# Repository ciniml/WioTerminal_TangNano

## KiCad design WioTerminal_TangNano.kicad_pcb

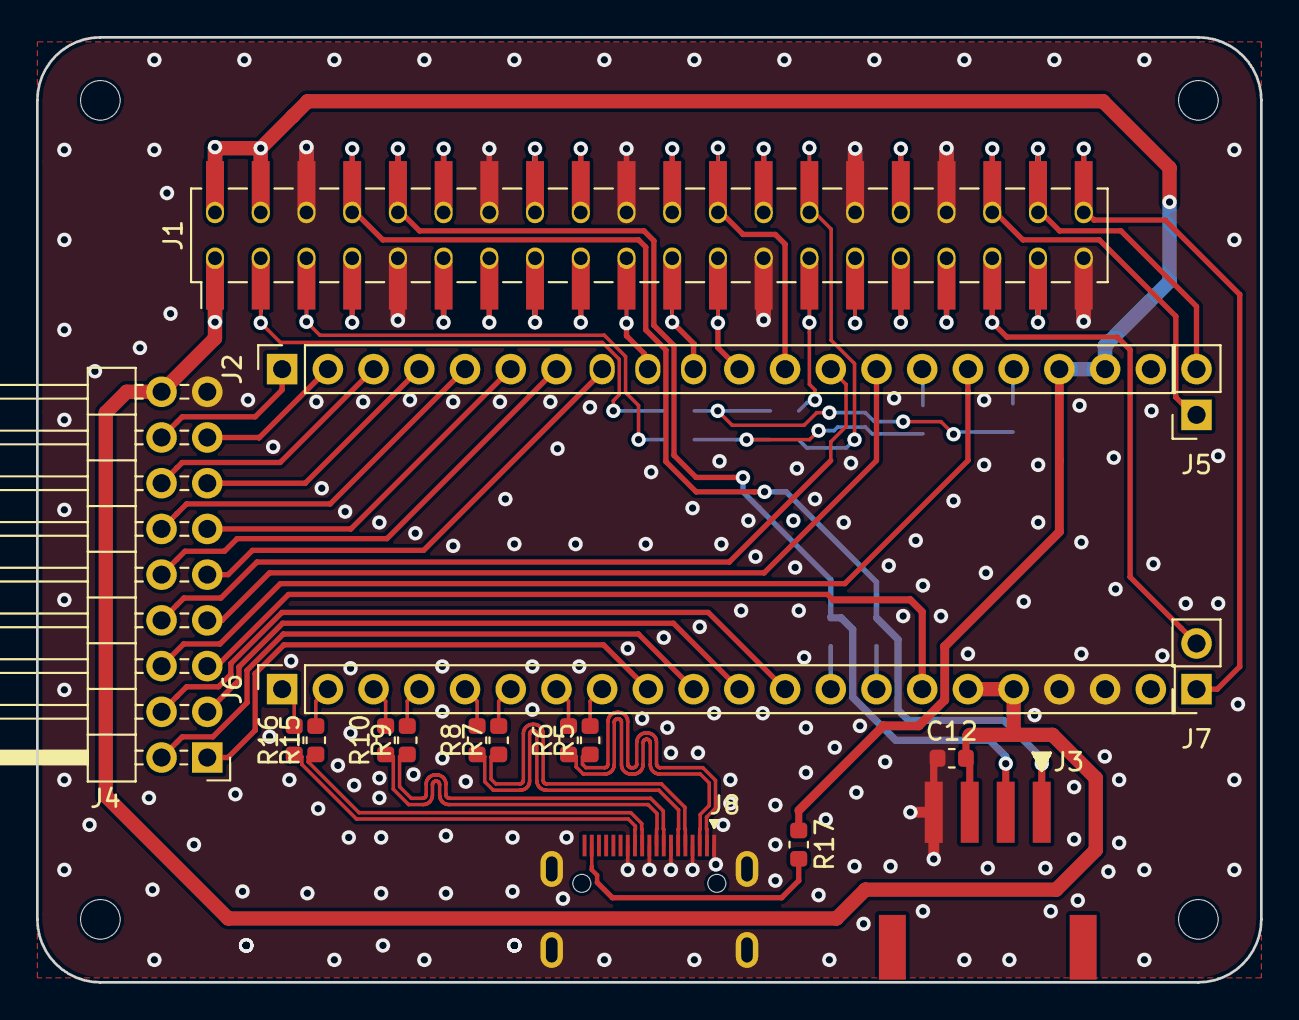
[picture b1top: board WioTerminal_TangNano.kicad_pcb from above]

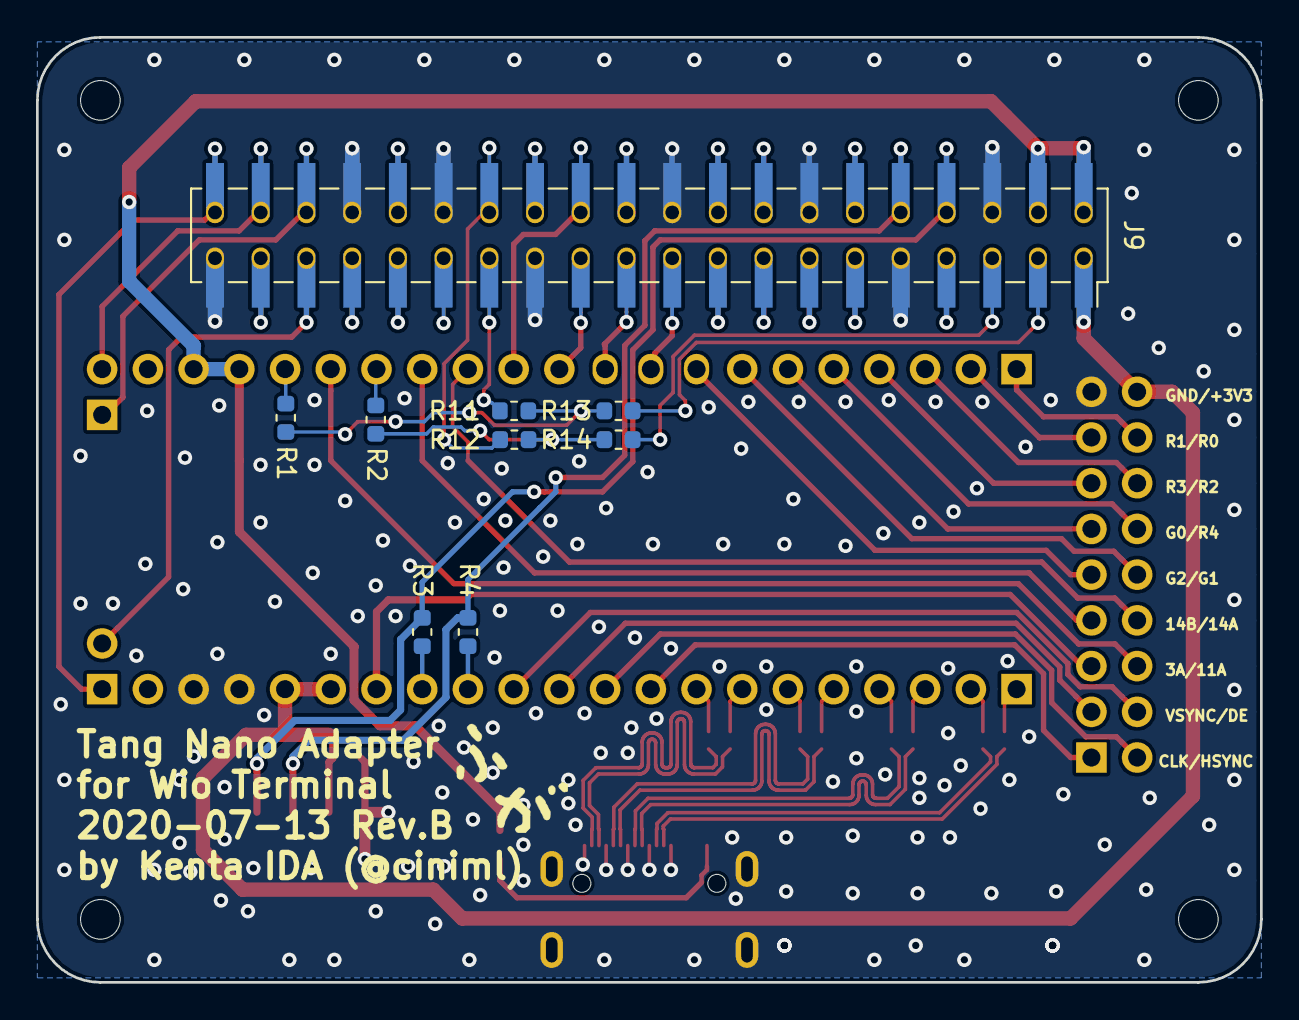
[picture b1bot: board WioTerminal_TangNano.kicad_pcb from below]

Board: 2 copper layers, 68.0 x 52.5 mm, 32 parts (10 on the bottom side), 70 nets.

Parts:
C12: 1u; C_0603_1608Metric
J1: Raspberry_Pi_2_3; PinHeader_2x20_P2.54mm_Vertical_SMD
J2: TangNano_Left; PinSocket_1x20_P2.54mm_Vertical
J3: GROVE; PHS-4AW
J4: Conn_01x18; PinHeader_2x09_P2.54mm_Horizontal
J5: TangNano_JTAG_L; PinSocket_1x02_P2.54mm_Vertical
J6: TangNano_Right; PinSocket_1x20_P2.54mm_Vertical
J7: TangNano_JTAG_R; PinSocket_1x02_P2.54mm_Vertical
J8: HDMI_C_1.3; SOFNG-HDMI-519
J9: Raspberry_Pi_2_3; PinSocket_2x20_P2.54mm_Vertical_SMD
LOGO1: Logo_Open_Hardware_Small; logo
MH1, MH2, MH3, MH4: Corner; MountingHole_2.2mm_M2_DIN965
R1, R2, R3, R4, R13, R14: DNP; R_0603_1608Metric
R5, R6, R7, R8, R9, R10, R15, R16: 240; R_0603_1608Metric
R11, R12: 0; R_0603_1608Metric
R17: 10; R_0603_1608Metric

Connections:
+3V3: C12.1, J1.1, J1.17, J3.3, J4.18, J6.16, J6.17, J9.1, J9.17
+5V: J1.2, J1.4, J2.18, J2.19, J9.2, J9.4, R17.1
/B0: J6.4, R9.2
/B1: J6.5, R8.2
/B2: J6.6, R7.2
/B3: J6.7, R6.2
/B4: J6.8, R5.2
/CE1: J1.26, J9.26
/CH552_RX0: J6.13, R4.1
/CH552_TX0: J6.14, R3.1
/G0: J2.6, J4.11
/G1: J2.7, J4.10
/G2: J2.8, J4.9
/G3: J6.1, R16.2
/G4: J6.2, R15.2
/G5: J6.3, R10.2
/GCLK0: J1.7, J9.7
/GCLK1: J1.29, J9.29
/GCLK2: J1.31, J9.31
/GPIO17: J1.11, J9.11
/GPIO18: J1.12, J9.12
/GPIO22: J1.15, J9.15
/GPIO23: J1.16, J9.16
/GPIO24: J1.18, J9.18
/GPIO25: J1.22, J9.22
/GPIO26: J1.37, J9.37
/GPIO27: J1.13, J9.13
/HDMI_CK_N: J8.12, R16.1
/HDMI_CK_P: J8.11, R15.1
/HDMI_D0_N: J8.9, R10.1
/HDMI_D0_P: J8.8, R9.1
/HDMI_D1_N: J8.6, R8.1
/HDMI_D1_P: J8.5, R7.1
/HDMI_D2_N: J8.3, R6.1
/HDMI_D2_P: J8.2, R5.1
/I2C0_SCL: J1.28, J9.28, R12.2
/I2C0_SDA: J1.27, J9.27, R11.2
/I2C1_SCL: J1.5, J9.5, R14.2
/I2C1_SDA: J1.3, J9.3, R13.2
/IOB3A: J4.5, J6.15
/IOB7A: J1.19, J2.9, J9.19
/IOB10A: J1.21, J2.10, J9.21
/IOB10B: J1.23, J2.11, J9.23
/IOB11B: J1.24, J2.12, J9.24
/IOB14A: J2.13, J4.8
/IOB14B: J2.14, J4.7
/IOB16A: J2.17, R1.1
/IOB16B: J2.15, R2.1
/IOV11A: J2.16, J4.6
/LCD_CLK: J4.1, J6.9
/LCD_DE: J4.4, J6.12
/LCD_HSYNC: J4.2, J6.10
/LCD_VSYNC: J4.3, J6.11
/PWM0: J1.32, J9.32
/PWM1: J1.33, J9.33
/R0: J2.1, J4.16
/R1: J2.2, J4.15
/R2: J2.3, J4.14
/R3: J2.4, J4.13
/R4: J2.5, J4.12
/RXD: J1.10, J3.2, J9.10, R4.2
/SCL: R2.2, R12.1, R14.1
/SDA: R1.2, R11.1, R13.1
/TCK: J1.40, J7.1, J9.40
/TDI: J1.38, J5.2, J9.38
/TDO: J1.35, J7.2, J9.35
/TMS: J1.36, J5.1, J9.36
/TXD: J1.8, J3.1, J9.8, R3.2
GND: C12.2, J1.6, J1.9, J1.14, J1.20, J1.25, J1.30, J1.34, J1.39, J3.4, J4.17, J6.18, J6.19, J8.1, J8.4, J8.7, J8.10, J8.13, J8.SH, J9.6, J9.9, J9.14, J9.20, J9.25, J9.30, J9.34, J9.39
unnamed: J8.18, R17.2

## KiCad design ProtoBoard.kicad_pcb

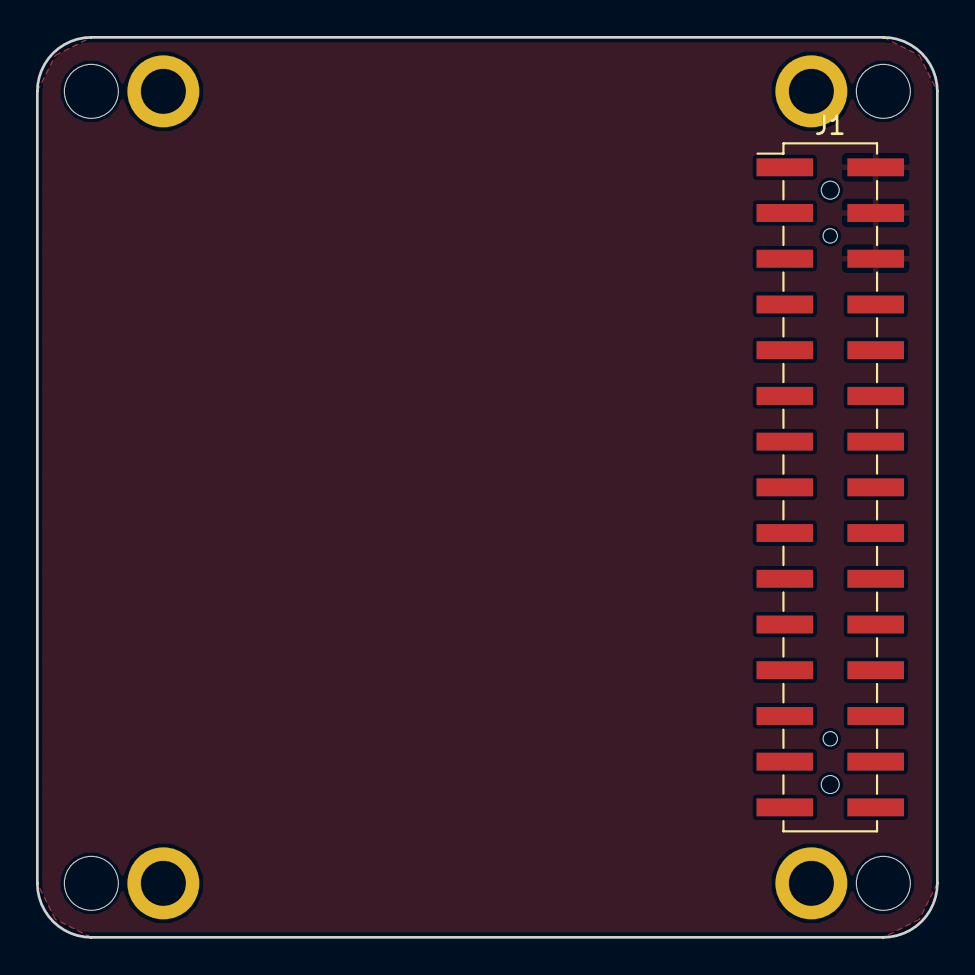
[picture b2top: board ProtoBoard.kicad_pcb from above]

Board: 2 copper layers, 50.0 x 50.0 mm, 10 parts (1 on the bottom side), 26 nets, no tracks yet.

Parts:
J1: MBUS_TOP; MBUS_Header
J2: MBUS_BOTTOM; MBUS_Socket
MH1, MH2, MH3, MH4: Corner; MountingHole_3mm
MH5, MH5#2, MH6, MH6#2: Fix; MountingHole_2.5mm

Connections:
+3V3: J1.11, J2.12
+5V: J1.27, J2.28
/ADC_G35: J1.1, J2.2
/ADC_G36: J1.3, J2.4
/BATTERY: J1.29, J2.30
/DAC: J1.9, J2.10
/DAC_SPK: J1.7, J2.8
/GPIO_G2: J1.20, J2.19
/GPIO_G5: J1.19, J2.20
/HPWR: J1.26, J1.28, J1.30, J2.25, J2.27, J2.29
/IIS_IN: J1.25, J2.26
/IIS_MK: J1.23, J2.24
/IIS_OUT: J1.24, J2.23
/IIS_SK: J1.22, J2.21
/IIS_WS: J1.21, J2.22
/MISO: J1.10, J2.9
/MOSI: J1.8, J2.7
/RST: J1.5, J2.6
/RXD0: J1.14, J2.13
/RXD2: J1.16, J2.15
/SCK: J1.12, J2.11
/SCL: J1.17, J2.18
/SDA: J1.18, J2.17
/TXD0: J1.13, J2.14
/TXD2: J1.15, J2.16
GND: J1.2, J1.4, J1.6, J2.1, J2.3, J2.5

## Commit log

2020-01-13 Copy from Wi-SUN repository
2020-06-14 Implementaing Tang Nano Adapter
2020-06-14 Routing finished
2020-06-14 Fix that TangNano board width was wrong.
2020-07-12 Add HDMI receptacle
2020-07-12 Fix that HDMI Type-C pin assignment was wrong. Add PTH to use concatenating header.
2020-07-12 Add footprint module
